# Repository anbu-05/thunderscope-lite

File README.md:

ad9288 can be replaced with ad9218 for higher resolution

the AFE is designed for 1GSPS so 100MSPS should work just fine

the STM32H523RETx can be replaced with STM32H562RGTx for higher performance

also you NEED to implement the microcontroller IC in the PCB because you need to make sure the all 8/10 of the ADC's output signals arrive at the same time

ad9288/9218 have different sampling rate options - but this requires changing out the CMOS oscillator accordinly as well. the current option is for a low jitter 100MHz clk signal: ASEM1-100.000MHZ-LC-T

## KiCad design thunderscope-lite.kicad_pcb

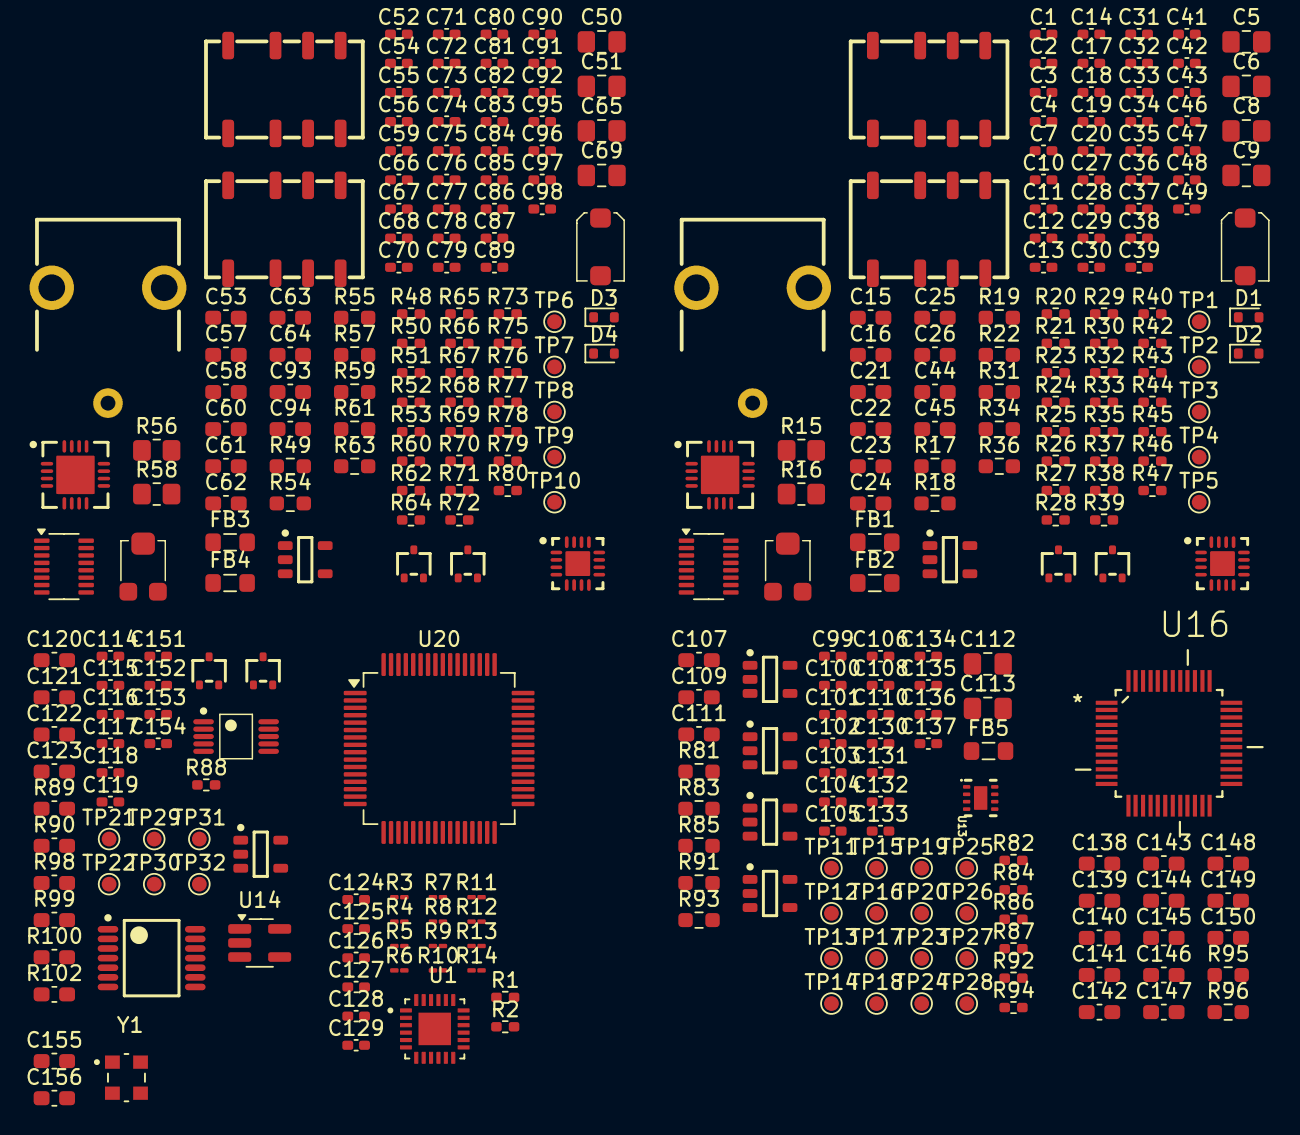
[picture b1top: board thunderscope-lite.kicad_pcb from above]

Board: 2 copper layers, 330 parts (0 on the bottom side), 150 nets, no tracks yet.

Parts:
C1, C56: 18pF; C_0402_1005Metric_Pad0.74x0.62mm_HandSolder
C2, C3, C13, C77, C80, C87: 3pF; C_0402_1005Metric_Pad0.74x0.62mm_HandSolder
C4, C81: 0.3pF; C_0402_1005Metric_Pad0.74x0.62mm_HandSolder
C5, C6, C8, C9, C50, C51, C65, C69: 22uF; C_0805_2012Metric_Pad1.18x1.45mm_HandSolder
C7, C10, C27, C28, C29, C30, C31, C32, C33, C34, C35, C36, C37, C38, C39, C46, C47, C48, C49, C52, C66, C67, C70, C71, C72, C73, C74, C75, C76, C78, C79, C82, C83, C85, C95, C96, C97, C98, C101, C102, C105, C106, C115, C116, C117, C124, C125, C126, C127, C128, C132, C133, C136, C137, C152, C154: 1uF; C_0402_1005Metric_Pad0.74x0.62mm_HandSolder
C11, C86: 1pF; C_0402_1005Metric_Pad0.74x0.62mm_HandSolder
C12, C84: 8pF; C_0402_1005Metric_Pad0.74x0.62mm_HandSolder
C14, C41, C42, C43, C89, C90, C91, C92, C118: 100nF; C_0402_1005Metric_Pad0.74x0.62mm_HandSolder
C15, C60: 1nF; C_0603_1608Metric_Pad1.08x0.95mm_HandSolder
C16, C53: 10nF; C_0603_1608Metric_Pad1.08x0.95mm_HandSolder
C17, C18, C20, C54, C59, C68, C119: 100pF; C_0402_1005Metric_Pad0.74x0.62mm_HandSolder
C19, C55: 68pF; C_0402_1005Metric_Pad0.74x0.62mm_HandSolder
C21, C22, C23, C24, C25, C26, C44, C45, C57, C58, C61, C62, C63, C64, C93, C94, C107, C109, C111, C120, C122, C141, C142, C156: 10uF; C_0603_1608Metric_Pad1.08x0.95mm_HandSolder
C40, C88: 2-6pF; EW_TRIMCAP
C99, C100, C103, C104, C108, C110, C114, C129, C130, C131, C134, C135, C151, C153: 10uF; C_0402_1005Metric_Pad0.74x0.62mm_HandSolder
C112, C113: 10uF; C_0805_2012Metric_Pad1.18x1.45mm_HandSolder
C121, C123: 1uF; C_0603_1608Metric_Pad1.08x0.95mm_HandSolder
C138, C139, C140, C143, C144, C145, C146, C147, C148, C149, C150: 100nF; C_0603_1608Metric_Pad1.08x0.95mm_HandSolder
C155: 0.1uF; C_0603_1608Metric_Pad1.08x0.95mm_HandSolder
D1, D2, D3, D4: 1N4148WT; D_SOD-523
FB1, FB2, FB3, FB4, FB5: 120@100MHZ; L_0805_2012Metric_Pad1.05x1.20mm_HandSolder
J1, J2: BNC; MOL_0731000105
K1, K2, K3, K4: UD2-4.5NUN-L; KEMET_UD2-4.5NUN-L
Q1, Q2, Q3, Q4, Q5, Q6: DMN62D0UW; GEN_SOT_323
R1, R2: 300R; R_0402_1005Metric_Pad0.72x0.64mm_HandSolder
R3, R4, R5, R6, R7, R8: 300R; R_01005_0402Metric_Pad0.57x0.30mm_HandSolder
R9, R10: 120R; R_01005_0402Metric_Pad0.57x0.30mm_HandSolder
R11, R12, R13, R14: 4.99R; R_01005_0402Metric_Pad0.57x0.30mm_HandSolder
R15, R56: 49.9R; R_0805_2012Metric_Pad1.20x1.40mm_HandSolder
R16, R58: 1MR; R_0805_2012Metric_Pad1.20x1.40mm_HandSolder
R17, R31, R55, R57: 30R; R_0603_1608Metric_Pad0.98x0.95mm_HandSolder
R18, R59: 15R; R_0603_1608Metric_Pad0.98x0.95mm_HandSolder
R19, R22, R49, R63: 22R; R_0603_1608Metric_Pad0.98x0.95mm_HandSolder
R20, R21, R23, R24, R52, R53, R64, R65: 10KR; R_0402_1005Metric_Pad0.72x0.64mm_HandSolder
R25, R46, R47, R60, R79, R80: 0R; R_0402_1005Metric_Pad0.72x0.64mm_HandSolder
R26, R43, R44, R66, R76, R77: 1K; R_0402_1005Metric_Pad0.72x0.64mm_HandSolder
R27, R28, R67, R68: 976K; R_0402_1005Metric_Pad0.72x0.64mm_HandSolder
R29, R70: 20K; R_0402_1005Metric_Pad0.72x0.64mm_HandSolder
R30, R50: 909K; R_0402_1005Metric_Pad0.72x0.64mm_HandSolder
R32, R38, R40, R51, R71, R75, R87: 90.9K; R_0402_1005Metric_Pad0.72x0.64mm_HandSolder
R33, R39, R45, R48, R72, R78, R82, R84, R92, R94: 10K; R_0402_1005Metric_Pad0.72x0.64mm_HandSolder
R34, R36, R54, R61: 10M; R_0603_1608Metric_Pad0.98x0.95mm_HandSolder
R35, R62: 2K; R_0402_1005Metric_Pad0.72x0.64mm_HandSolder
R37, R69: 35.7K; R_0402_1005Metric_Pad0.72x0.64mm_HandSolder
R41, R74: 2K TRIMPOT; BOU_3mm_POT
R42, R73: 49.9K; R_0402_1005Metric_Pad0.72x0.64mm_HandSolder
R81, R83, R85, R91, R93: 0.01R; R_0603_1608Metric_Pad0.98x0.95mm_HandSolder
R86: 280K; R_0402_1005Metric_Pad0.72x0.64mm_HandSolder
R88: 100R; R_0402_1005Metric_Pad0.72x0.64mm_HandSolder
R89, R90: 10K; C_0603_1608Metric_Pad1.08x0.95mm_HandSolder
R95: 23.2K; R_0603_1608Metric_Pad0.98x0.95mm_HandSolder
R96: 10K; R_0603_1608Metric_Pad0.98x0.95mm_HandSolder
R98, R99, R100, R102: 4.7K; C_0603_1608Metric_Pad1.08x0.95mm_HandSolder
TP1, TP2, TP3, TP4, TP5, TP6, TP7, TP8, TP9, TP10, TP11, TP12, TP13, TP14, TP15, TP16, TP17, TP18, TP19, TP20, TP21, TP22, TP23, TP24, TP25, TP26, TP27, TP28, TP29, TP30, TP31, TP32: TestPoint; TestPoint_Pad_D1.0mm
U1: ADA4930-2YCPZ-R2; QFN50P400X400X100-25N
U2: MCP4728; MC_MSOP10_UN
U3, U7: TMUX4053; TI_TSOT-23-16_DYY0016A
U4, U8, U15: OPA140AIDBVR; GEN_SOT23_5_950_2900X1600X1450
U5, U9: BUF802; TI_VQFN_RGT0016C
U6, U10: LMH6518; TI_WQFN_RGH0016A
U11, U12, U17, U18: NCP161ASN330T1G; GEN_SOT23_5_950_2900X1600X1450
U13: LM27761; TI_WSON8_DSG0008A
U14: REF2025; SOT-23-5_HandSoldering
U16: AD9218BSTZ-105; QFP50P900X900X160-48N
U19: MCP4452-104E; MC_TSSOP14
U20: STM32H562RGTx; LQFP-64_10x10mm_P0.5mm
Y1: ASEM1-100.000MHZ-LC-T; XTAL_ASEM1-100.000MHZ-LC-T

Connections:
+3V3_ACQ: C101.1, C102.1, C126.1, C127.1, C128.1, C129.1, TP13.1, U1.3 (+VS1), U1.4 (+VS1), U1.9 (+VS2), U1.10 (+VS2), U1.14 (*PD2), U1.20 (*PD1), U11.5 (OUT)
+3V3_PGA: C49.2, C98.2, Q3.2 (G), Q4.2 (G), R45.2, R78.2, R99.1, R100.1, U6.12 (VDD), U10.12 (VDD)
+3V3_VD: C132.1, C133.1, C142.2, C144.2, C146.2, C148.2, C150.2, R95.1, TP25.1, U16.13 (VD_2), U16.30 (VD_3), U16.31 (VD), U16.48 (VD_4), U17.5 (OUT)
+3V3_VDD: C136.1, C137.1, C141.1, C143.1, C145.1, C147.1, C149.1, C155.1, C156.1, TP28.1, U16.15 (VDD), U16.28 (VDD_3), U16.33 (VDD_2), U16.46 (VDD_4), U18.5 (OUT), Y1.1 (STANDBY), Y1.4 (VDD)
+5V: C5.1, C8.1, C21.2, C22.2, C23.2, C27.2, C28.2, C29.2, C30.2, C31.2, C32.2, C39.2, C44.2, C50.1, C57.2, C61.2, C63.2, C65.1, C66.2, C70.2, C73.2, C75.2, C78.2, C82.2, C85.2, C93.2, C114.1, C115.1, C120.1, C121.1, C151.1, C152.1, C153.1, C154.1, FB2.1, FB4.1, R19.1, R22.1, R49.1, R63.1, R81.1, R83.1, R85.1, R91.1, R93.1, R98.1, R102.1, TP11.1, TP14.1, TP17.1, TP23.1, TP26.1, U2.1 (VDD), U3.16 (VDD), U4.5 (V+), U5.1 (Vs+), U5.12 (Vso+), U5.15 (CLH), U7.16 (VDD), U8.5 (V+), U9.1 (Vs+), U9.12 (Vso+), U9.15 (CLH), U14.3 (EN), U14.4 (IN), U15.5 (V+), U19.12 (VDD)
+VBIAS: C117.1, R89.2, TP21.1, U14.5 (Vref)
-5V: C24.1, C25.1, C26.1, C33.1, C34.1, C35.1, C36.1, C37.1, C38.1, C58.1, C62.1, C64.1, C67.1, C71.1, C74.1, C76.1, C79.1, C83.1, C110.1, C112.1, C113.1, C122.2, C123.2, FB5.2, R37.1, R69.1, TP20.1, U3.7 (VSS), U4.2 (V-), U5.5 (Vs-), U5.6 (Aux_Bias), U5.8 (Vs-), U5.10 (Vso-), U7.7 (VSS), U8.2 (V-), U9.5 (Vs-), U9.6 (Aux_Bias), U9.8 (Vs-), U9.10 (Vso-), U15.2 (V-)
-VBIAS: C14.2, C41.2, C89.2, C91.2, C118.1, R40.1, R43.2, R44.2, R75.1, R76.2, R77.2, R88.1, TP22.1
/ACQ and FE Voltage Regs/+5V_R_CP: C107.1, R85.2, TP18.1, U13.1 (VIN)
/ACQ and FE Voltage Regs/ACQ_EN: R82.2, U11.3 (EN)
/ACQ and FE Voltage Regs/PGA_EN: R84.2, U12.3 (EN)
/ACQ and FE Voltage Regs/VDD_EN: R94.2, U18.3 (EN)
/ACQ and FE Voltage Regs/VD_EN: R92.2, U17.3 (EN)
/ADC driver/IN1_N: R3.1, R9.1, R47.1
/ADC driver/IN1_P: R2.1, R9.2, R46.1
/ADC driver/IN2_N: R7.1, R10.1, R80.1
/ADC driver/IN2_P: R6.1, R10.2, R79.1
/ADC driver/OUT1_N: R11.2, U16.3 (~AINA)
/ADC driver/OUT1_P: R12.2, U16.2 (AINA)
/ADC driver/OUT2_N: R13.2, U16.10 (~AINB)
/ADC driver/OUT2_P: R14.2, U16.11 (AINB)
/ADC/ENC: U16.14 (ENCB), U16.47 (ENCA), Y1.3 (OUTPUT)
/CH1/+VPGA: C45.2, C46.2, C47.2, C48.2, FB2.2, U6.3 (VCC), U6.4 (VCC)
/CH1/ATTEN: R23.2, R24.1, TP2.1
/CH1/ATTEN_1X: K1.4, K1.5
/CH1/ATTEN_50X_IN: C3.2, C4.2, K1.2, R26.2, R27.2
/CH1/ATTEN_50X_OUT: C11.1, C13.1, C40.1, K1.7, R27.1, R29.1
/CH1/ATTEN_IN: K1.3, K3.6
/CH1/ATTEN_OUT: K1.6, R30.2, R31.1
/CH1/BNC_IN: J2.1 (Signal), K3.3
/CH1/BUF_IN: C15.2, R36.1, U5.2 (IN)
/CH1/BUF_IN_AUX: C20.2, R35.2, U5.4 (IN_Aux)
/CH1/BUF_IN_BIAS: R36.2, U5.3 (IN_Bias)
/CH1/BUF_OUT: R38.2, R42.2, U5.11 (OUT)
/CH1/BUF_OUT_R: R42.1, U6.6 (IN_P)
/CH1/DC_CPL: R33.2, TP3.1, U3.9 (SEL3), U3.10 (SEL2), U3.11 (SEL1)
/CH1/DC_FB: C17.1, U3.15 (D2), U4.4 (-)
/CH1/PGA_BIAS: C43.2, FB1.2, R43.1, R44.1, TP4.1, U6.7 (IN_N)
/CH1/PGA_CSn: R45.1, TP5.1, U6.9 (CSn)
/CH1/TERM: R20.1, R21.2, TP1.1
/CH1/TERM_1M: K3.2, R17.1
/CH1/TERM_50Z: C1.1, K3.4, R15.1, R18.1
/CH1/TERM_50Z_R: K3.5, R18.2, R25.2
/CH2/+VPGA: C94.2, C95.2, C96.2, C97.2, FB4.2, U10.3 (VCC), U10.4 (VCC)
/CH2/ATTEN: R64.2, R65.1, TP8.1
/CH2/ATTEN_1X: K4.4, K4.5
/CH2/ATTEN_50X_IN: C80.2, C81.2, K4.2, R66.2, R67.2
/CH2/ATTEN_50X_OUT: C86.1, C87.1, C88.1, K4.7, R67.1, R70.1
/CH2/ATTEN_IN: K2.6, K4.3
/CH2/ATTEN_OUT: K4.6, R50.2, R57.1
/CH2/BNC_IN: J1.1 (Signal), K2.3
/CH2/BUF_IN: C60.2, R61.1, U9.2 (IN)
/CH2/BUF_IN_AUX: C68.2, R62.2, U9.4 (IN_Aux)
/CH2/BUF_IN_BIAS: R61.2, U9.3 (IN_Bias)
/CH2/BUF_OUT: R71.2, R73.2, U9.11 (OUT)
/CH2/BUF_OUT_R: R73.1, U10.6 (IN_P)
/CH2/DC_CPL: R48.2, TP6.1, U7.9 (SEL3), U7.10 (SEL2), U7.11 (SEL1)
/CH2/DC_FB: C59.1, U7.15 (D2), U8.4 (-)
/CH2/PGA_BIAS: C92.2, FB3.2, R76.1, R77.1, TP10.1, U10.7 (IN_N)
/CH2/PGA_CSn: R78.1, TP9.1, U10.9 (CSn)
/CH2/TERM: R52.2, R53.1, TP7.1
/CH2/TERM_1M: K2.2, R55.1
/CH2/TERM_50Z: C56.1, K2.4, R56.1, R59.1
/CH2/TERM_50Z_R: K2.5, R59.2, R60.2
/Front End Trim and Bias/TRIM_SCL: Q4.3 (S), R99.2, TP31.1
/Front End Trim and Bias/TRIM_SCL_5V: Q4.1 (D), R102.2, TP29.1, U2.2 (SCL), U19.4 (SCL)
/Front End Trim and Bias/TRIM_SDA: Q3.3 (S), R100.2, TP32.1
/Front End Trim and Bias/TRIM_SDA_5V: Q3.1 (D), R98.2, TP30.1, U2.3 (SDA), U19.5 (SDA)
/Front End Trim and Bias/US-: C119.1, R89.1, R90.2, U15.3 (+)
/Front End Trim and Bias/VOUT1: U2.6 (VOUTA), U19.13 (P2B)
/Front End Trim and Bias/VOUT2: U2.7 (VOUTB), U19.10 (P0B)
/Front End Trim and Bias/VOUT3: U2.8 (VOUTC), U19.7 (P1B)
/Front End Trim and Bias/VOUT4: U2.9 (VOUTD), U19.2 (P3B)
/TRIM_1: C42.2, FB1.1, U19.14 (P2W)
/TRIM_2: C90.2, FB3.1, U19.9 (P0W)
/VCM: C124.1, C125.1, R95.2, R96.1, U1.11 (VOCM2), U1.17 (VOCM1), U6.13 (VCM), U10.13 (VCM)
GND: C2.1, C5.2, C6.2, C7.2, C8.2, C9.2, C10.2, C12.2, C13.2, C14.1, C20.1, C21.1, C22.1, C23.1, C24.2, C25.2, C26.2, C27.1, C28.1, C29.1, C30.1, C31.1, C32.1, C33.2, C34.2, C35.2, C36.2, C37.2, C38.2, C39.1, C40.2, C41.1, C42.1, C43.1, C44.1, C45.1, C46.1, C47.1, C48.1, C49.1, C50.2, C51.2, C52.2, C57.1, C58.2, C61.1, C62.2, C63.1, C64.2, C65.2, C66.1, C67.2, C68.1, C69.2, C70.1, C71.2, C72.2, C73.1, C74.2, C75.1, C76.2, C77.1, C78.1, C79.2, C82.1, C83.2, C84.2, C85.1, C87.2, C88.2, C89.1, C90.1, C91.1, C92.1, C93.1, C94.1, C95.1, C96.1, C97.1, C98.1, C99.2, C100.2, C101.2, C102.2, C103.2, C104.2, C105.2, C106.2, C107.2, C109.2, C110.2, C111.2, C112.2, C113.2, C114.2, C115.2, C116.2, C117.2, C118.2, C120.2, C121.2, C122.1, C123.1, C124.2, C125.2, C126.2, C127.2, C128.2, C129.2, C130.2, C131.2, C132.2, C133.2, C134.2, C135.2, C136.2, C137.2, C138.2, C139.2, C140.2, C141.2, C142.1, C143.2, C144.1, C145.2, C146.1, C147.2, C148.1, C149.2, C150.1, C151.2, C152.2, C153.2, C154.2, C155.2, C156.2, J1.2 (SHIELD), J2.2 (SHIELD), Q1.3 (S), Q2.3 (S), Q5.3 (S), Q6.3 (S), R15.2, R16.2, R21.1, R23.1, R29.2, R32.1, R33.1, R34.1, R41.3, R48.1, R51.1, R52.1, R54.1, R56.2, R58.2, R64.1, R70.2, R74.3, R82.1, R84.1, R87.1, R92.1, R94.1, R96.2, U1.15 (-VS2), U1.16 (-VS2), U1.21 (-VS1), U1.22 (-VS1), U1.25 (EPAD), U2.4 (LDACn), U2.10 (VSS), U3.6 (~EN), U3.8 (GND), U5.14 (CLL), U5.17 (PAD), U6.5 (GND), U6.8 (GND), U6.17 (PAD), U7.6 (~EN), U7.8 (GND), U9.14 (CLL), U9.17 (PAD), U10.5 (GND), U10.8 (GND), U10.17 (PAD), U11.2 (GND), U12.2 (GND), U13.2 (GND), U13.9 (PAD), U14.2 (GND), U15.4 (-), U16.1 (GND_7), U16.12 (GND_4), U16.16 (GND_6), U16.27 (GND_3), U16.29 (GND_8), U16.32 (GND_2), U16.34 (GND), U16.45 (GND_5), U17.2 (GND), U18.2 (GND), U19.3 (HVC/A0), U19.6 (VSS), U19.11 (A1), U20.12 (VSSA), U20.18 (VSS), U20.31 (VSS), U20.47 (VSS), U20.63 (VSS), Y1.2 (GND)
unnamed: C1.2, R25.1
unnamed: C2.2, R26.1
unnamed: C4.1, R28.2
unnamed: C3.1, C11.2, C12.1, R28.1
unnamed: C15.1, R31.2
unnamed: C56.2, R60.1
unnamed: C60.1, R57.2
unnamed: C77.2, R66.1
unnamed: C80.1, C84.1, C86.2, R68.1
unnamed: C81.1, R68.2
unnamed: D1.2 (A), K3.8, Q5.1 (D)
unnamed: C6.1, C7.1, D1.1 (K), K3.1, R19.2
unnamed: D2.2 (A), K1.8, Q1.1 (D)
unnamed: C9.1, C10.1, D2.1 (K), K1.1, R22.2
unnamed: D3.2 (A), K2.8, Q6.1 (D)
unnamed: C51.1, C52.1, D3.1 (K), K2.1, R49.2
unnamed: D4.2 (A), K4.8, Q2.1 (D)
unnamed: C69.1, C72.1, D4.1 (K), K4.1, R63.2
unnamed: K2.7, R55.2, R58.1
unnamed: K3.7, R16.1, R17.2
unnamed: Q1.2 (G), R24.2
unnamed: Q2.2 (G), R65.2
unnamed: Q5.2 (G), R20.2
unnamed: Q6.2 (G), R53.2
unnamed: R38.1, R39.2, R40.2
unnamed: R39.1, R41.1, R41.2
unnamed: R71.1, R72.2, R75.2
unnamed: R72.1, R74.1, R74.2
unnamed: R4.2, U1.2 (+FB1)
unnamed: R8.2, U1.8 (+FB2)
unnamed: R1.1, R2.2, U1.24 (+IN1)
unnamed: R5.1, R6.2, U1.6 (+IN2)
unnamed: R14.1, U1.18 (+OUT1)
unnamed: R12.1, U1.12 (+OUT2)
unnamed: R1.2, U1.23 (-FB1)
unnamed: R5.2, U1.5 (-FB2)
unnamed: R3.2, R4.1, U1.1 (-IN1)
unnamed: R7.2, R8.1, U1.7 (-IN2)
unnamed: R13.1, U1.19 (-OUT1)
unnamed: R11.1, U1.13 (-OUT2)
unnamed: C16.1, R30.1, R32.2, U3.14 (D1)
unnamed: C17.2, R35.1, U3.4 (D3), U4.1 (OUT)
unnamed: C16.2, R34.2, U3.13 (S1B), U4.3 (+)
unnamed: C18.1, U3.2 (S2A)
unnamed: C19.1, U3.1 (S2B)
unnamed: C18.2, U3.5 (S3A)
unnamed: C19.2, U3.3 (S3B)
unnamed: R37.2, U5.7 (R_Bias)
unnamed: R47.2, U6.14 (OUT_N)
unnamed: R46.2, U6.15 (OUT_P)
unnamed: C53.1, R50.1, R51.2, U7.14 (D1)
unnamed: C59.2, R62.1, U7.4 (D3), U8.1 (OUT)
unnamed: C53.2, R54.2, U7.13 (S1B), U8.3 (+)
unnamed: C54.1, U7.2 (S2A)
unnamed: C55.1, U7.1 (S2B)
unnamed: C54.2, U7.5 (S3A)
unnamed: C55.2, U7.3 (S3B)
unnamed: R69.2, U9.7 (R_Bias)
unnamed: R80.2, U10.14 (OUT_N)
unnamed: R79.2, U10.15 (OUT_P)
unnamed: C99.1, C100.1, R81.2, TP12.1, U11.1 (IN)
unnamed: C103.1, C104.1, R83.2, TP15.1, U12.1 (IN)
unnamed: C108.1, U13.8 (C1+)
unnamed: C108.2, U13.7 (C1-)
unnamed: C109.1, U13.3 (CPOUT)
unnamed: R86.1, R87.2, U13.5 (VFB)
unnamed: C111.1, FB5.1, R86.2, TP19.1, U13.4 (VOUT)
unnamed: C116.1, U14.1 (Vbias)
unnamed: C119.2, R88.2, R90.1, U15.1 (OUT)
unnamed: C138.1, C139.1, C140.1, U16.5 (REFINA), U16.6 (REFOUT), U16.7 (REFINB)
unnamed: C130.1, C131.1, R91.2, TP24.1, U17.1 (IN)
unnamed: C134.1, C135.1, R93.2, TP27.1, U18.1 (IN)
PGA: C105.1, C106.1, TP16.1, U12.5 (OUT)
